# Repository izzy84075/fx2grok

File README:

-------------------------------------------------------------------------------
README
-------------------------------------------------------------------------------

The sigrok project aims at creating a portable, cross-platform,
Free/Libre/Open-Source signal analysis software suite that supports various
device types (such as logic analyzers, oscilloscopes, multimeters, and more).

The fx2grok device is intended to be the tinyiest possible Open Hardware FX2
eval board (that can be used as 8-channel logic analyzer).

Using the open-source fx2lafw firmware (and sigrok, of course) you can use
this device as 8-channel logic analyzer.

Status
------

fx2grok is currently work in progress. The PCB layout is not yet finished
and no prototypes have yet been made.

Schematics, PCB layout
----------------------

The schematics and PCB layout are available from the fx2grok git repo:

  $ git clone git://sigrok.org/fx2grok

Copyright and license
---------------------

The fx2grok schematics and layout are done from scratch in Kicad, and are
released under the CC-BY-SA 3.0 license.

They are Copyright (C) 2012-2017 Uwe Hermann <uwe@hermann-uwe.de>.

Mailing list
------------

 https://lists.sourceforge.net/lists/listinfo/sigrok-devel

IRC
---

You can find the sigrok developers in the #sigrok IRC channel on Freenode.

Website
-------

 http://sigrok.org/wiki/Fx2grok

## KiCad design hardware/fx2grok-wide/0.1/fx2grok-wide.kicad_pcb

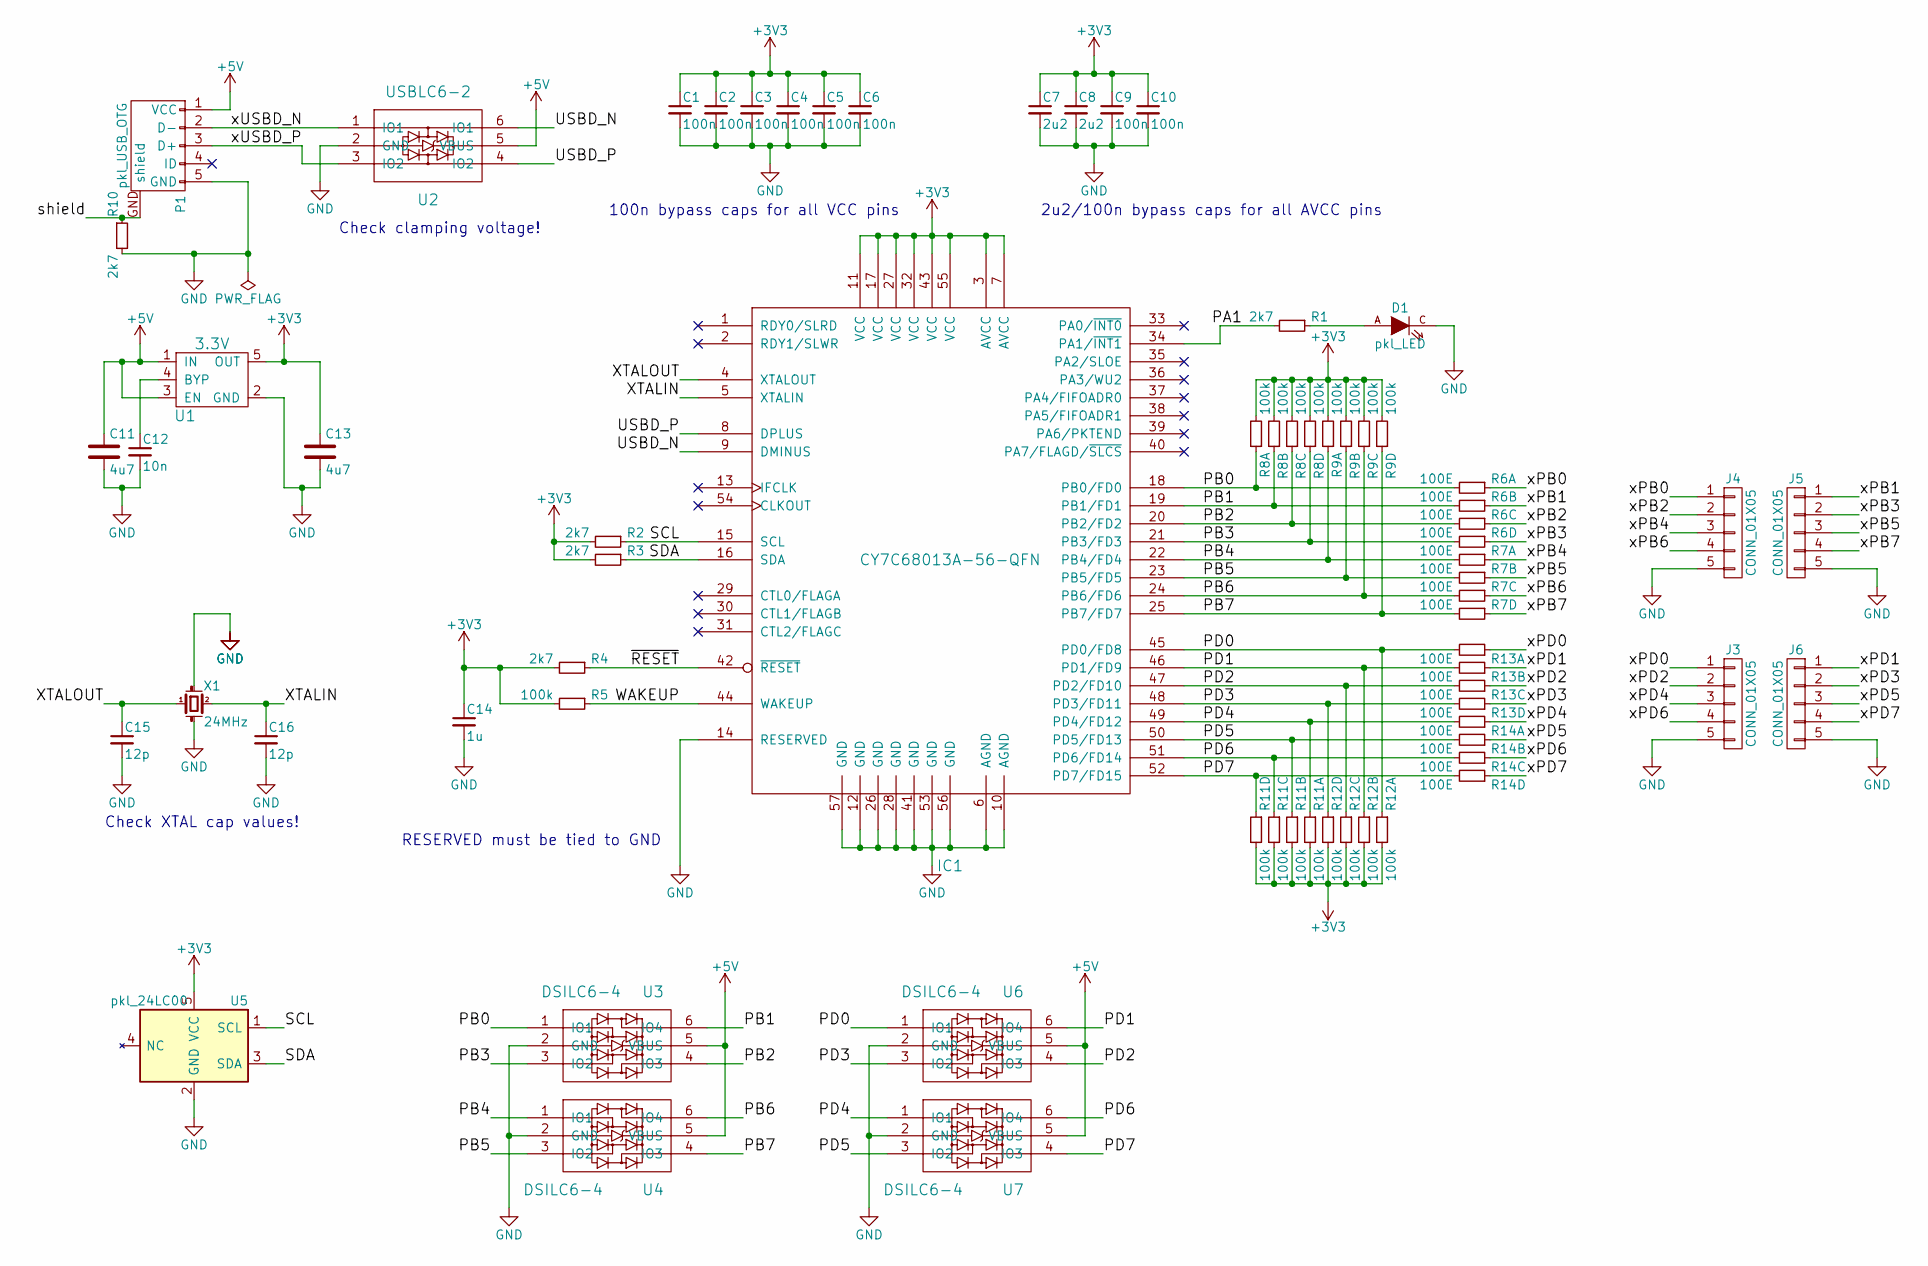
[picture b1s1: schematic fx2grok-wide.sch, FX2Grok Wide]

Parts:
C1, C2, C3, C4, C5, C6, C9, C10: 100n; C_0402
C7, C8: 2u2; C_0402
C11, C13: 4u7; C_0603
C12: 10n; C_0402
C14: 1u; C_0402
C15, C16: 12p; C_0402
D1: pkl_LED; D_0603
IC1: CY7C68013A-56-QFN; QFN-56-1EP_8x8mm_Pitch0.5mm
J3, J4, J5, J6: CONN_01X05; Pin_Header_Angled_1x05_Pitch1.27mm_SMD
P1: pkl_USB_OTG; Connector_USB_Micro_B_SMD
R1, R2, R3, R4, R10: 2k7; R_0402
R5: 100k; R_0402
R6, R7, R13, R14: 100E; R_Array_Convex_4x0402
R8, R9, R11, R12: 100k; R_Array_Convex_4x0402
U1: 3.3V; SOT-23-5
U2: USBLC6-2; SOT-666
U3, U4, U6, U7: DSILC6-4; SOT-666
U5: pkl_24LC00; SOT-23-5
X1: 24MHz; ABM8

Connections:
+3V3: C1.1, C2.1, C3.1, C4.1, C5.1, C6.1, C7.1, C8.1, C9.1, C10.1, C13.1, C14.1, IC1.3 (AVCC), IC1.7 (AVCC), IC1.11 (VCC), IC1.17 (VCC), IC1.27 (VCC), IC1.32 (VCC), IC1.43 (VCC), IC1.55 (VCC), R2.2, R3.2, R4.2, R5.2, R8.2, R8.4, R8.6, R8.8, R9.2, R9.4, R9.6, R9.8, R11.2, R11.4, R11.6, R11.8, R12.2, R12.4, R12.6, R12.8, U1.5 (OUT), U5.5 (VCC)
+5V: C11.1, P1.1 (VCC), U1.1 (IN), U1.3 (EN), U2.5 (VBUS), U3.5 (VBUS), U4.5 (VBUS), U6.5 (VBUS), U7.5 (VBUS)
/PB0: IC1.18 (PB0/FD0), R6.2, R8.1, U3.1 (IO1)
/PB1: IC1.19 (PB1/FD1), R6.4, R8.3, U3.6 (IO4)
/PB2: IC1.20 (PB2/FD2), R6.6, R8.5, U3.4 (IO3)
/PB3: IC1.21 (PB3/FD3), R6.8, R8.7, U3.3 (IO2)
/PB4: IC1.22 (PB4/FD4), R7.2, R9.1, U4.1 (IO1)
/PB5: IC1.23 (PB5/FD5), R7.4, R9.3, U4.3 (IO2)
/PB6: IC1.24 (PB6/FD6), R7.6, R9.5, U4.6 (IO4)
/PB7: IC1.25 (PB7/FD7), R7.8, R9.7, U4.4 (IO3)
/PD0: IC1.45 (PD0/FD8), R12.1, R13.2, U6.1 (IO1)
/PD1: IC1.46 (PD1/FD9), R12.3, R13.4, U6.6 (IO4)
/PD2: IC1.47 (PD2/FD10), R12.5, R13.6, U6.4 (IO3)
/PD3: IC1.48 (PD3/FD11), R12.7, R13.8, U6.3 (IO2)
/PD4: IC1.49 (PD4/FD12), R11.1, R14.2, U7.1 (IO1)
/PD5: IC1.50 (PD5/FD13), R11.3, R14.4, U7.3 (IO2)
/PD6: IC1.51 (PD6/FD14), R11.5, R14.6, U7.6 (IO4)
/PD7: IC1.52 (PD7/FD15), R11.7, R14.8, U7.4 (IO3)
/SCL: IC1.15 (SCL), R2.1, U5.1 (SCL)
/SDA: IC1.16 (SDA), R3.1, U5.3 (SDA)
/USBD_N: IC1.9 (DMINUS), U2.6 (IO1)
/USBD_P: IC1.8 (DPLUS), U2.4 (IO2)
/WAKEUP: IC1.44 (WAKEUP), R5.1
/XTALIN: C16.1, IC1.5 (XTALIN), X1.2
/XTALOUT: C15.1, IC1.4 (XTALOUT), X1.1
/shield: P1.GND (shield), R10.1
/xPB0: J4.1, R6.1
/xPB1: J5.1, R6.3
/xPB2: J4.2, R6.5
/xPB3: J5.2, R6.7
/xPB4: J4.3, R7.1
/xPB5: J5.3, R7.3
/xPB6: J4.4, R7.5
/xPB7: J5.4, R7.7
/xPD0: J3.1, R13.1
/xPD1: J6.1, R13.3
/xPD2: J3.2, R13.5
/xPD3: J6.2, R13.7
/xPD4: J3.3, R14.1
/xPD5: J6.3, R14.3
/xPD6: J3.4, R14.5
/xPD7: J6.4, R14.7
/xUSBD_N: P1.2 (D-), U2.1 (IO1)
/xUSBD_P: P1.3 (D+), U2.3 (IO2)
/~RESET: IC1.42 (~RESET), R4.1
GND: C1.2, C2.2, C3.2, C4.2, C5.2, C6.2, C7.2, C8.2, C9.2, C10.2, C11.2, C12.2, C13.2, C14.2, C15.2, C16.2, D1.C, IC1.6 (AGND), IC1.10 (AGND), IC1.12 (GND), IC1.14 (RESERVED), IC1.26 (GND), IC1.28 (GND), IC1.41 (GND), IC1.53 (GND), IC1.56 (GND), IC1.57 (GND), J3.5, J4.5, J5.5, J6.5, P1.5 (GND), R10.2, U1.2 (GND), U2.2 (GND), U3.2 (GND), U4.2 (GND), U5.2 (GND), U6.2 (GND), U7.2 (GND), X1.GND (case)
unnamed: C12.1, U1.4 (BYP)
unnamed: D1.A, R1.1
unnamed: IC1.34 (PA1/~INT1), R1.2

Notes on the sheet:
RESERVED must be tied to GND
100n bypass caps for all VCC pins
2u2/100n bypass caps for all AVCC pins
Check XTAL cap values!
Check clamping voltage!

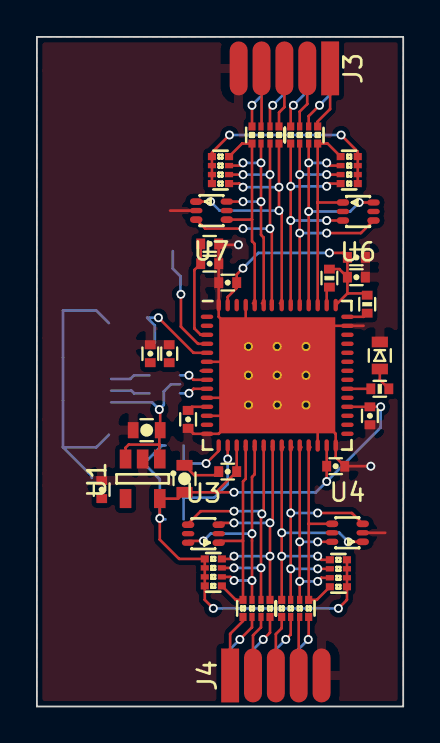
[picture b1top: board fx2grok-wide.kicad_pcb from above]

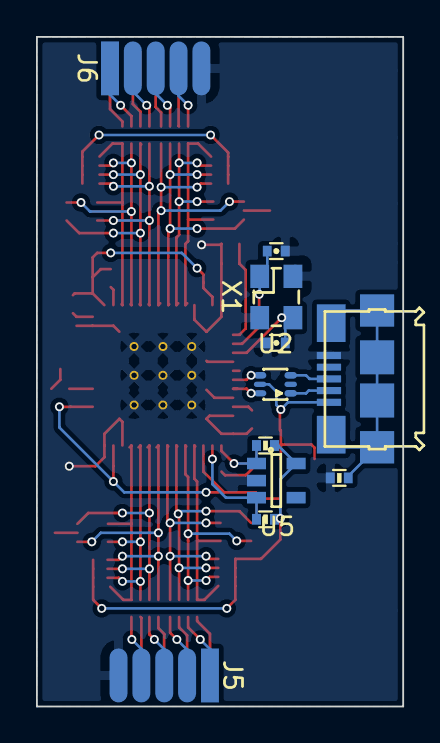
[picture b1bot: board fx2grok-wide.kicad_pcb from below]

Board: 2 copper layers, 20.3 x 37.2 mm, 45 parts (11 on the bottom side), 49 nets.

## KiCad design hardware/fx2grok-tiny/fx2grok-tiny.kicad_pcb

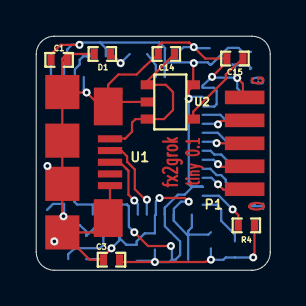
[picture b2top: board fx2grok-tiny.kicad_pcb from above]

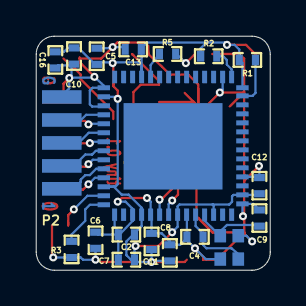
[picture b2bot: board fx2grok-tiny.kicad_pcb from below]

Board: 2 copper layers, 13.0 x 13.0 mm, 28 parts (19 on the bottom side), 22 nets.

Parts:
C1, C14: 1uF; SM0402
C2, C5, C7, C8, C10, C11, C12, C13, C15: 100nF; SM0402
C3, C6, C16: 2.2uF; SM0402
C4, C9: 12pF; SM0402
D1: LED1; SM0402
IC1: CY7C68013A-56; QFN56
P1, P2: CONN_01X05; CONN-5x1-SMD-127MM
R1: 100K; SM0402
R2, R3, R4, R5: 2K7; SM0402
U1: MICRO-USB-B-SMD
U2: MIC5319; SOT23-5
Y1: 24MHz; ABM11

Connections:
+3V3: C1.1, C2.1, C3.1, C5.1, C6.1, C7.1, C8.1, C10.1, C11.1, C12.1, C13.1, C16.1, IC1.3, IC1.7, IC1.11, IC1.17, IC1.27, IC1.32, IC1.43, IC1.55, R1.1, R2.1, R3.2, R4.2, U2.5
+5V: C14.1, U1.1, U2.1, U2.3
/DM: IC1.9, U1.2
/DP: IC1.8, U1.3
/PA0: IC1.33, R5.2
/PB0: IC1.18, P1.1
/PB1: IC1.19, P2.5
/PB2: IC1.20, P1.2
/PB3: IC1.21, P2.4
/PB4: IC1.22, P1.3
/PB5: IC1.23, P2.3
/PB6: IC1.24, P1.4
/PB7: IC1.25, P2.2
/RESET#: IC1.42, R2.2
/SCL: IC1.15, R3.1
/SDA: IC1.16, R4.1
/WAKEUP: IC1.44, R1.2
/XTALIN: C4.1, IC1.5, Y1.1
/XTALOUT: C9.1, IC1.4, Y1.3
GND: C1.2, C2.2, C3.2, C4.2, C5.2, C6.2, C7.2, C8.2, C9.2, C10.2, C11.2, C12.2, C13.2, C14.2, C15.2, C16.2, D1.2, IC1.6, IC1.10, IC1.12, IC1.14, IC1.26, IC1.28, IC1.41, IC1.53, IC1.56, P1.5, P2.1, U1.5, U2.2, Y1.2, Y1.4
unnamed: C15.1, U2.4
unnamed: D1.1, R5.1

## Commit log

2012-06-01 Add empty Kicad project.
2012-06-01 Add empty schematics.
2012-06-01 Add initial Cypress CY7C68013A-56 symbol.
2012-06-01 Move files to 0.1 subdir.
2012-06-01 Add fx2grok-cube.lib library to project.
2012-06-01 Add MINI-USB-B-SMD symbol to library.
2012-06-01 Add TLV1117-33 symbol to library.
2012-06-01 Place FX2, TLV1117, and USB connector components.
2012-06-01 Fill background of FX2 component.
2012-06-01 Add initial TLV1117 circuitry.
2012-06-01 Add initial USB connector circuitry.
2012-06-01 Add initial XTAL circuitry.
2012-06-01 Add VCC/GND circuitry, mark PA0-7/PD0-7 as no-connect.
2012-06-01 lib: FX2 symbol: Nicer active-low pin marking.
2012-06-02 Add a README.
2012-06-02 Add I2C pullups (2.2kOhm).
    Yes, they're needed even though we don't have an I2C EEPROM, see FX2 docs.
2012-06-02 FX2: The RESERVED pin needs to be tied to GND.
    (see FX2 docs)
2012-06-02 FX2: The WAKEUP pin is tied to VCC via a 100K resistor.
2012-06-02 Add 100nF bypass caps for all VCC pins.
2012-06-02 2.2uF/100nF for all AVCC pins (as per docs).
2012-06-02 Use 12pF load capacitors for the crystal.
2012-06-02 Various updates, move stuff around, add pin names.
2012-06-02 RESET# is tied to VCC via a resistor.
2012-06-02 FX2: Use "IC", not "U" for the chip refdes.
2012-06-02 Change Mini-USB B to Micro-USB B connector.
2012-06-03 Replace TLV1117 with MIC5319.
2012-06-03 Add a power LED.
2012-06-03 Add two optional general-purpose LEDs (PD0/1).
2012-06-03 Add resistorpack (8 x 100 Ohm) to PB0-PB7.
2012-06-03 Add footprints for all 0603 parts.
2012-06-03 Bugfix: USB shield pins were not properly connected.
2012-06-03 Fix a few pin types.
2012-06-03 Mark a few more pins as no-connect for now.
2012-06-03 Add some more footprints for symbols.
2012-06-03 Add a MICRO-USB-B-SMD footprint to a new library.
2012-06-03 Add new footprint library to project.
2012-06-03 schematic: Add PWR_FLAG (Kicad-internal stuff).
2012-06-03 schematic: Various fixes, add metadata.
2012-06-03 Add missing footprint for the resistorpack.
2012-06-03 schematic: Annotate all components.
    (i.e. turn C? and R? etc. into C12, R27 and so on)
2012-06-03 Generate netlist.
2012-06-03 Add empty PCB.
2012-06-03 Add RPACK-8-SMD-0603 footprint.
2012-06-03 Add AMB11 footprint (crystal).
2012-06-03 Add QFN56 (0.5mm pin spacing) footprint.
2012-06-03 schematic: RESET# needs a 2K7 and 1uF (TRM, p. 83).
    Thanks Joel Holdsworth <joel@airwebreathe.org.uk> for pointing this out.
2012-06-03 Re-run 'Annotate schematic'.
2012-06-03 Micro-USB B SMD footprint: Add missing SHIELD pin numbers.
2012-06-03 Bugfix: Replace 2-pin CRYSTAL with 4-pin QUARTZCMS4.
2012-06-03 Re-create netlist.
2012-06-03 PCB: Set DRC values (min. widths etc).
2012-06-03 PCB: Read in netlist.
2012-06-03 PCB: Disperse parts a bit.
2012-06-04 Start arranging parts.
2012-06-04 schematics: Change all 0603 parts to 0402.
2012-06-04 Regenerate netlist.
2012-06-04 Update PCB due to netlist changes.
2012-06-04 Add RPACK-8-SMD-0402 footprint.
2012-06-04 schematics: Replace 0603 resistorpack with 0402 one.
2012-06-04 schematics: Add 10pin connector for the probes.
2012-06-04 Update netlist.
2012-06-04 Add CONN-5x2-SMD-127MM footprint.
2012-06-04 Re-read netlist in the PCB.
2012-06-04 PCB: Tigthen DRC settings.
    Use 6mil trace width and trace spacing, 0.3mm min. via diameter,
    0.5 min. hole diameter.
2012-06-05 Draw 16mm x 12mm PCB borders (for now).
2012-06-05 schematics: Fix typo.
2012-06-05 Stuff everything into 12mm x 12mm PCB borders.
2012-06-06 Start arranging components (unfinished).
2012-10-23 schematic: Various simplifications and fixes, regen netlist.
    Drop two LEDs to save space. Use only one pullup for both SCL and SDA
    (should work as I2C is not used anyway). Probe connector: pins 9 + 10 are GND.
    Remove unneeded resistor/bridge for the USB connector SHIELD/GND connection.
2012-10-23 Switch 5mil tracks, 0.2mm vias (0.25mm restring).
2012-10-23 Update PCB to new netlist.
2012-10-23 First unfinished attempt at routing the board.
2012-10-23 README: Update description and git URL.
2012-10-23 Schematics: Fix wiki page URL.
2013-03-25 Schematics: Drop resistor-pack for now.
    The first version (probably all versions) will not have this, since it's
    optional and not strictly required to get an operational device.
2013-03-25 Update PCB layout (removed resistor-pack).
2013-03-26 Replace 5x2 SMD connector with two 5x1 pins/pads.
    We'll use a 5x2 pin header (1.27mm pitch) for now, soldering one 5x1
    half on the top side of the PCB, the other 5x1 on the bottom side of
    the PCB.
2013-04-04 Various updates.
    - Bring back one extra pullup resistor for SCL/SDA.
    - Small fixes and various rearrangements of the PCB components.
2013-04-06 PCB: Arrange and connect various parts/pins.
2013-04-26 README: Add "Copyright and license" section.
2014-07-22 Drop references to obsolete sigrok-commits mailing list.
2017-07-09 schematics: Load and resave via Kicad 4.0.5, fixup broken items.
    Fix broken wires, fix missing or broken symbols, update some symbols to
    the current Kicad versions, re-run "annotate schematic".
2017-07-09 layout: Load and resave via Kicad 4.0.5, update from netlist.
2017-07-09 Rename fx2grok-cube to fx2grok-tiny.
2017-07-09 fx2grok-tiny: Drop obsolete "special" library reference.
2017-07-09 Add local footprint library reference.
2017-07-09 Convert legacy footprint library to current Kicad format.
2017-07-09 layout: Re-read netlist.
2017-07-09 Replace crystal symbol with a 4-pin SMD crystal variant.
2017-09-07 fx2grok-tiny.sch: Bump date to today.
2017-09-07 Drop files that are no longer used.
2017-09-07 Finish initial layout, fixup various details.
2017-09-07 Move files out of 0.1 directory.
2017-09-07 README: Bump copyright year.
2017-09-07 Set solder mask clearance to 2mil / 0.05mm.
2017-09-07 Set board thickness to 0.8mm.
    This is required so that the 2x5 1.27mm pin headers will fit.
2017-09-07 Layer setup: Disable unused layers.
2017-09-07 List the board dimensions on the drawings layer.
2017-09-07 Run "Cleanup tracks and vias".
2017-09-07 Drop unneeded netlist file, it's considered a temporary file.
2017-09-07 Plot Gerber files, generate drill files.
2017-09-07 Rename old layer names to new F.Cu and B.Cu.
2017-09-07 Move silkscreen items to usable positions.
2017-09-07 Move/resize "fx2grok" text to avoid overlap with silkscreen.
2017-09-07 Set grid origin to lower-left corner of the PCB.
2017-09-08 Use rounded PCB edges, minor other improvements.
2017-09-08 Add 0/1/GND pin markings on the 5x2 1.27mm connector.
2017-09-08 Fix C16 silkscreen placement.
2017-09-08 Avoid P1/P2 silkscreen overlapping the 0/1/G copper markings.
2017-09-08 Regenerate Gerber files.
2017-09-08 Added solder stop openings over copper legend text.
    It is necessary to add openings in the solder stop to text on the copper
    layer, otherwise it is not readable.
2017-09-08 schematics: Change LDO to Micrel MIC5504.
    300mA should be enough, and this one is cheaper and we can also drop
    one of the capacitors as well.
2017-09-08 layout: Update due to MIC5504 change, minor USB connector fixup.
2017-09-14 Added gitignore for kicad backup and net files.
2017-09-14 Added pretty-kicad-libs library submodule.
2017-09-14 Initial commit of fx2grok-flat.
2017-09-16 Updated PKL.
2017-09-16 Recreated original schematic + input protection.
2017-09-17 Added eeprom and pullups on probe inputs. Started routing.
2017-10-03 Add the first version of the schematic for the fx2grok-wide.
2017-10-04 Switch the LED to PA1, and start laying out the PCB.
2017-10-06 Switch to a different footprint for the FX2, and make the input connectors SMD pads on both sides of the PCB(Can stick a 2x5 through-hole header over the side of the PCB and solder it on). Made a bun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
2017-10-06 Switch back to the old FX2 footprint, add the center pad of the QFN to the schematic symbol, and connect it to ground as recommended by Cypress. And connect a few more traces.

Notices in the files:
hardware/fx2grok-wide/0.1/fx2grok-wide.sch:
CC-BY-SA V4.0
